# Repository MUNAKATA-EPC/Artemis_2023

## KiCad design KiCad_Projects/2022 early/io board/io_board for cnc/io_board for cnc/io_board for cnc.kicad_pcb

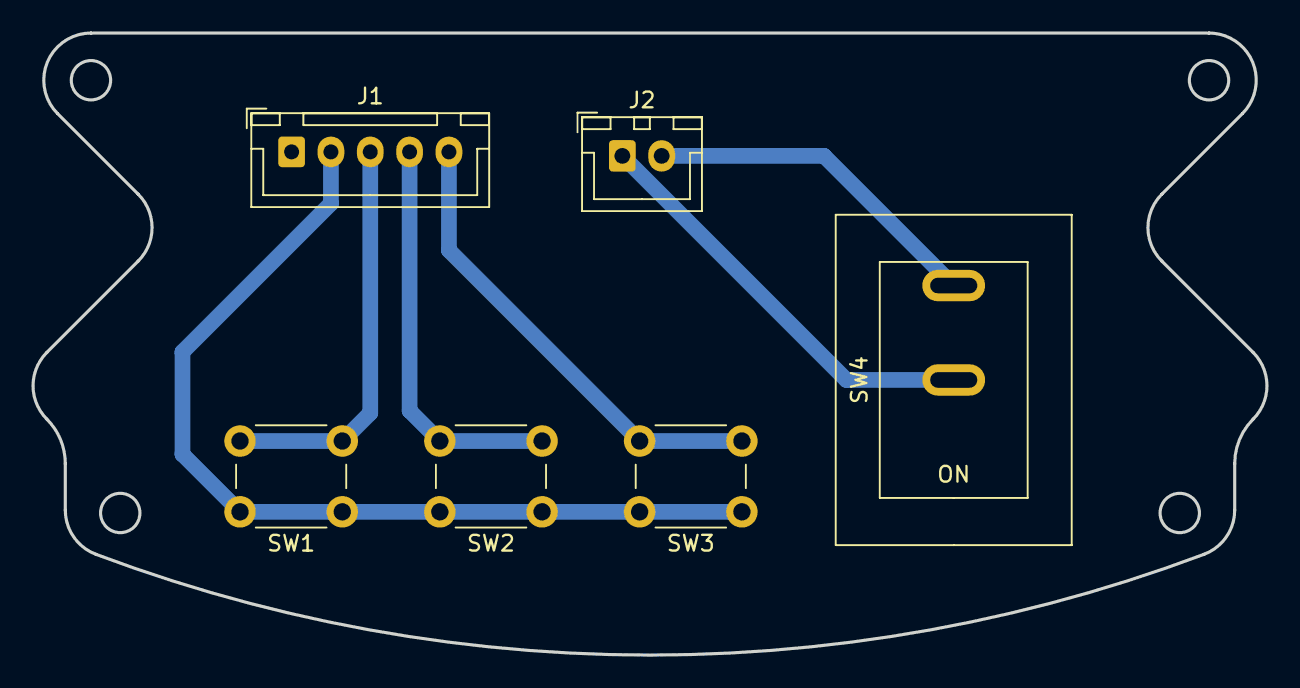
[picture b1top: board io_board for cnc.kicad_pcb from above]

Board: 2 copper layers, 78.4 x 39.5 mm, 6 parts (0 on the bottom side), 6 nets.

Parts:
J1: Conn_01x05_Female; JST_XH_B5B-XH-A_1x05_P2.50mm_Vertical
J2: Conn_01x02_Female; JST_XH_B2B-XH-A_1x02_P2.50mm_Vertical
SW1, SW2, SW3: SW_DIP_x01; SW_PUSH_6mm_H5mm
SW4: SW_DIP_x01; DS-850k

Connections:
+5V: J1.2, SW1.1, SW2.1, SW3.1
+7.5V: J2.2, SW4.2
GND: J2.1, SW4.1
SW1: J1.3, SW1.2
SW2: J1.4, SW2.2
SW3: J1.5, SW3.2

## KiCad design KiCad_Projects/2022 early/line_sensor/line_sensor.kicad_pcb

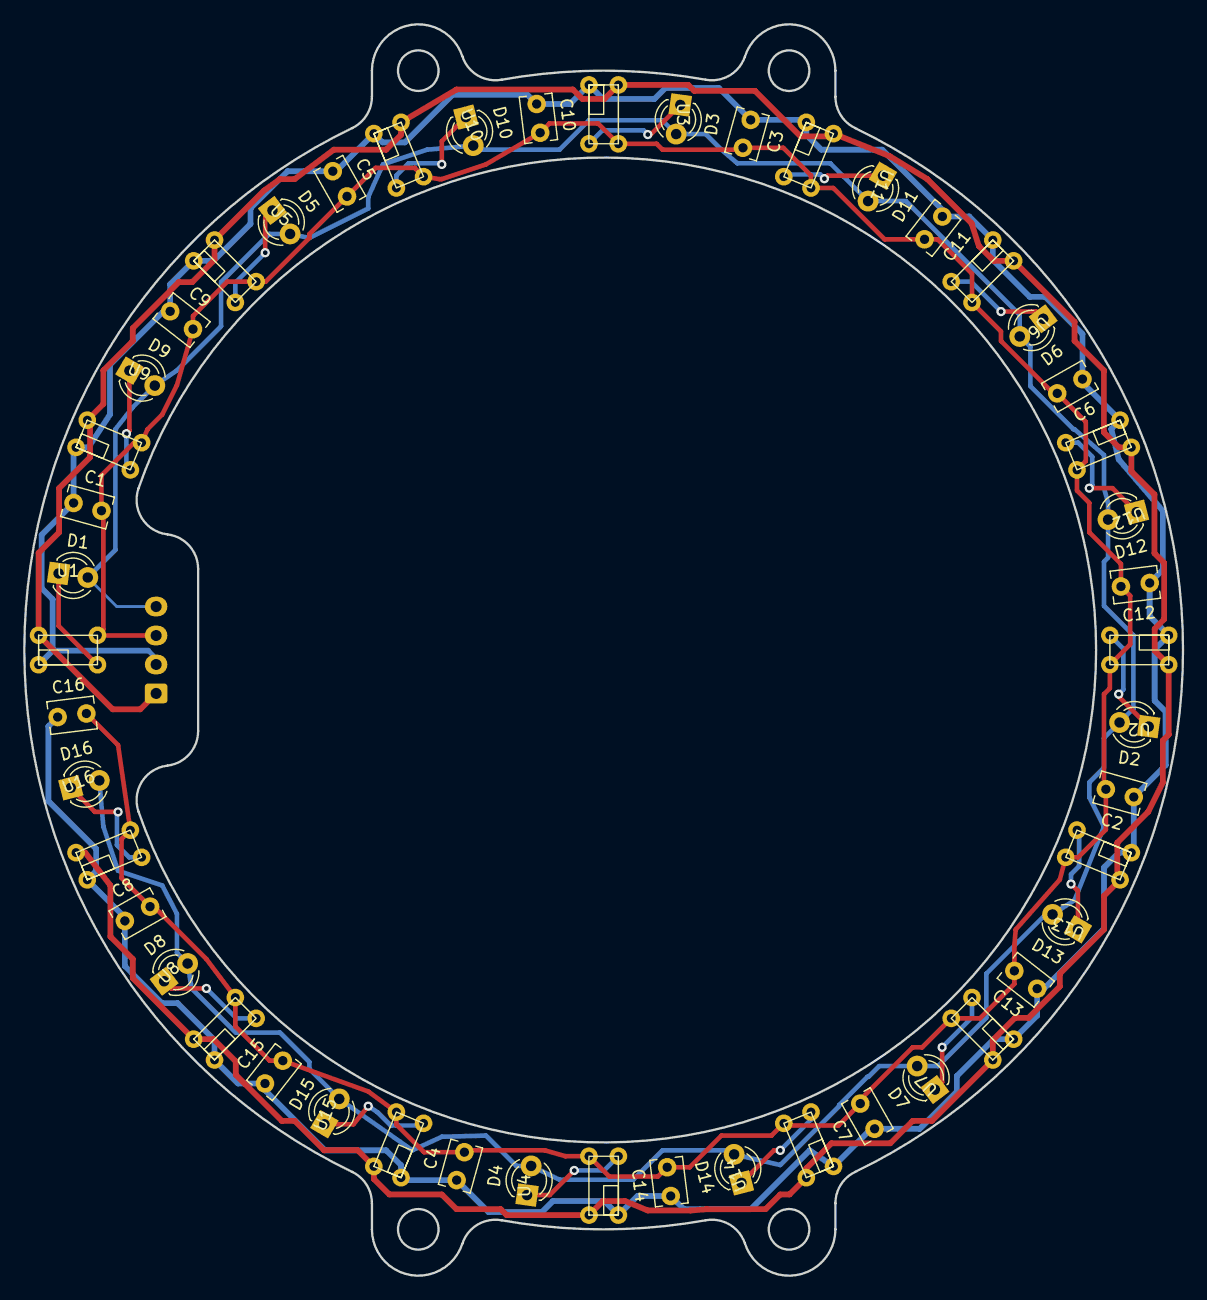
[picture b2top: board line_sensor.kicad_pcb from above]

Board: 2 copper layers, 100.0 x 108.0 mm, 49 parts (1 on the bottom side), 20 nets.

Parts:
C1, C2, C3, C4, C5, C6, C7, C8, C9, C10, C11, C12, C13, C14, C15, C16: C_Small; C_Disc_D3.8mm_W2.6mm_P2.50mm
D1, D2, D3, D4, D5, D6, D7, D8, D9, D10, D11, D12, D13, D14, D15, D16: LED; LED_D3.0mm_Clear
J1: Conn_01x04_Female; JST_XH_B4B-XH-A_1x04_P2.50mm_Vertical
U1, U2, U3, U4, U5, U6, U7, U8, U9, U10, U11, U12, U13, U14, U15, U16: S4282-51; Line_sennsor

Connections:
1: J1.1, U1.3 (Vout), U2.3 (Vout), U3.3 (Vout), U4.3 (Vout), U5.3 (Vout), U6.3 (Vout), U7.3 (Vout), U8.3 (Vout), U9.3 (Vout), U10.3 (Vout), U11.3 (Vout), U12.3 (Vout), U13.3 (Vout), U14.3 (Vout), U15.3 (Vout), U16.3 (Vout)
5: D1.2 (A), D2.2 (A), D3.2 (A), D4.2 (A), D5.2 (A), D6.2 (A), D7.2 (A), D8.2 (A), D9.2 (A), D10.2 (A), D11.2 (A), D12.2 (A), D13.2 (A), D14.2 (A), D15.2 (A), D16.2 (A), J1.4
+5V: C1.2, C2.2, C3.2, C4.2, C5.2, C6.2, C7.2, C8.2, C9.2, C10.2, C11.2, C12.2, C13.2, C14.2, C15.2, C16.2, J1.3, U1.2 (Vcc), U2.2 (Vcc), U3.2 (Vcc), U4.2 (Vcc), U5.2 (Vcc), U6.2 (Vcc), U7.2 (Vcc), U8.2 (Vcc), U9.2 (Vcc), U10.2 (Vcc), U11.2 (Vcc), U12.2 (Vcc), U13.2 (Vcc), U14.2 (Vcc), U15.2 (Vcc), U16.2 (Vcc)
GND: C1.1, C2.1, C3.1, C4.1, C5.1, C6.1, C7.1, C8.1, C9.1, C10.1, C11.1, C12.1, C13.1, C14.1, C15.1, C16.1, J1.2, U1.4 (GND), U2.4 (GND), U3.4 (GND), U4.4 (GND), U5.4 (GND), U6.4 (GND), U7.4 (GND), U8.4 (GND), U9.4 (GND), U10.4 (GND), U11.4 (GND), U12.4 (GND), U13.4 (GND), U14.4 (GND), U15.4 (GND), U16.4 (GND)
unnamed: D1.1 (K), U1.1 (K(-))
unnamed: D2.1 (K), U2.1 (K(-))
unnamed: D3.1 (K), U3.1 (K(-))
unnamed: D4.1 (K), U4.1 (K(-))
unnamed: D5.1 (K), U5.1 (K(-))
unnamed: D6.1 (K), U6.1 (K(-))
unnamed: D7.1 (K), U7.1 (K(-))
unnamed: D8.1 (K), U8.1 (K(-))
unnamed: D9.1 (K), U9.1 (K(-))
unnamed: D10.1 (K), U10.1 (K(-))
unnamed: D11.1 (K), U11.1 (K(-))
unnamed: D12.1 (K), U12.1 (K(-))
unnamed: D13.1 (K), U13.1 (K(-))
unnamed: D14.1 (K), U14.1 (K(-))
unnamed: D15.1 (K), U15.1 (K(-))
unnamed: D16.1 (K), U16.1 (K(-))

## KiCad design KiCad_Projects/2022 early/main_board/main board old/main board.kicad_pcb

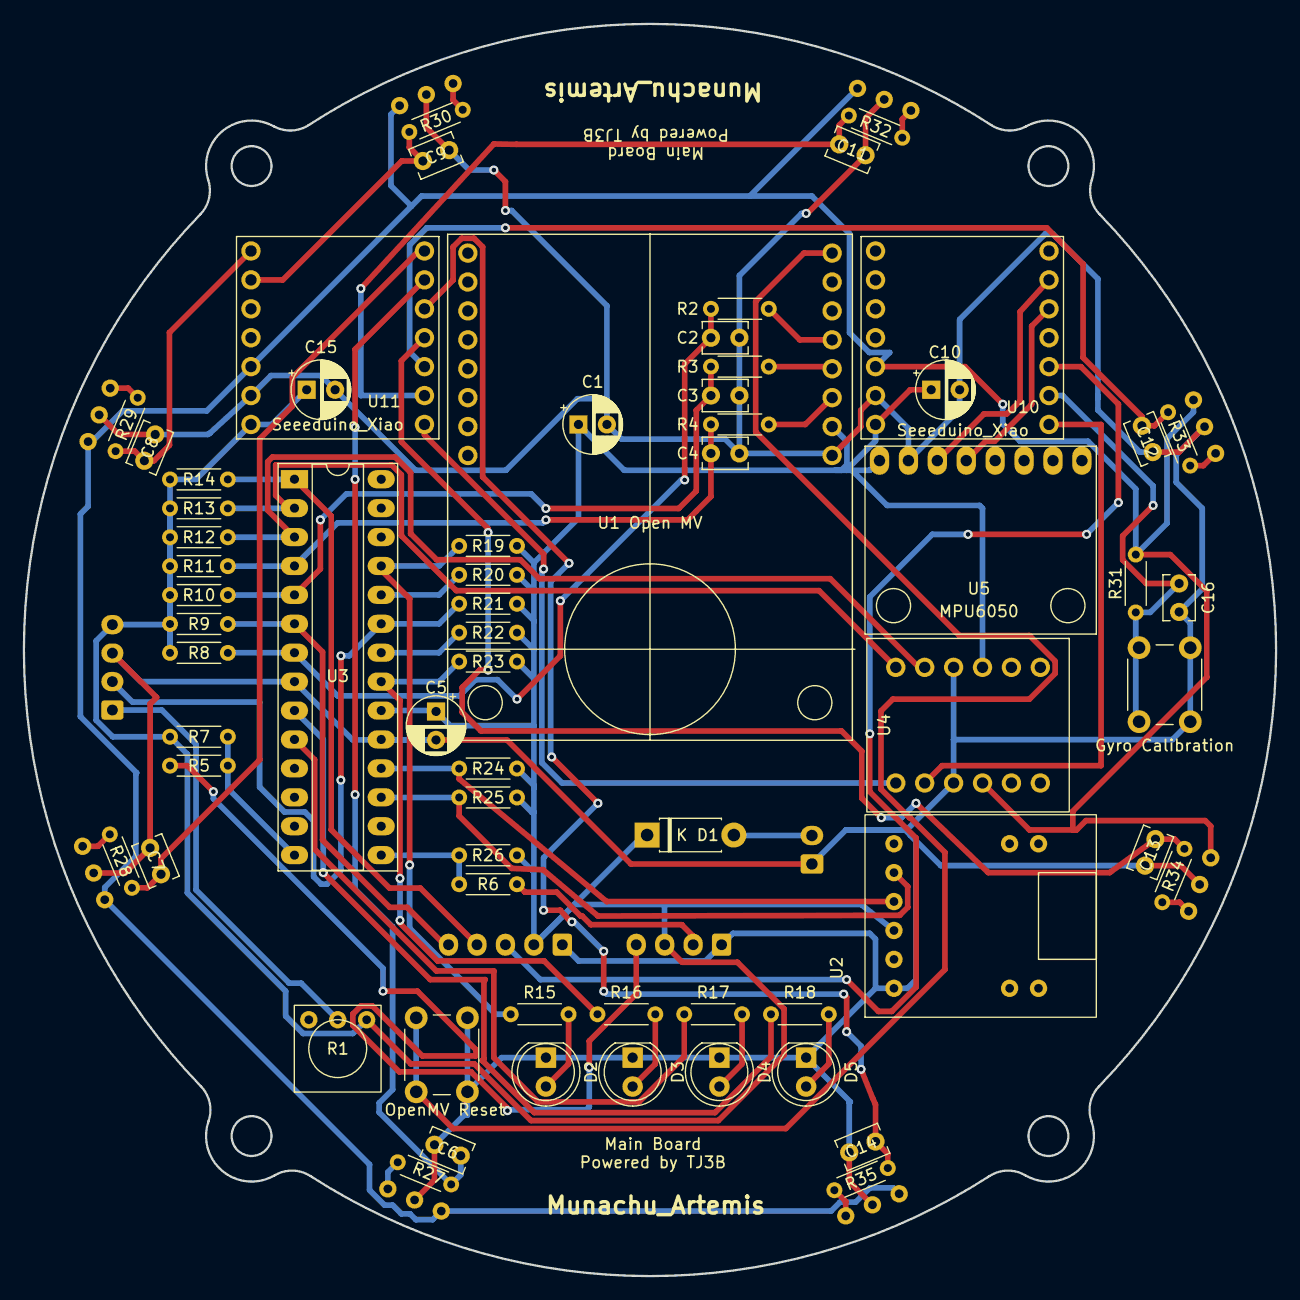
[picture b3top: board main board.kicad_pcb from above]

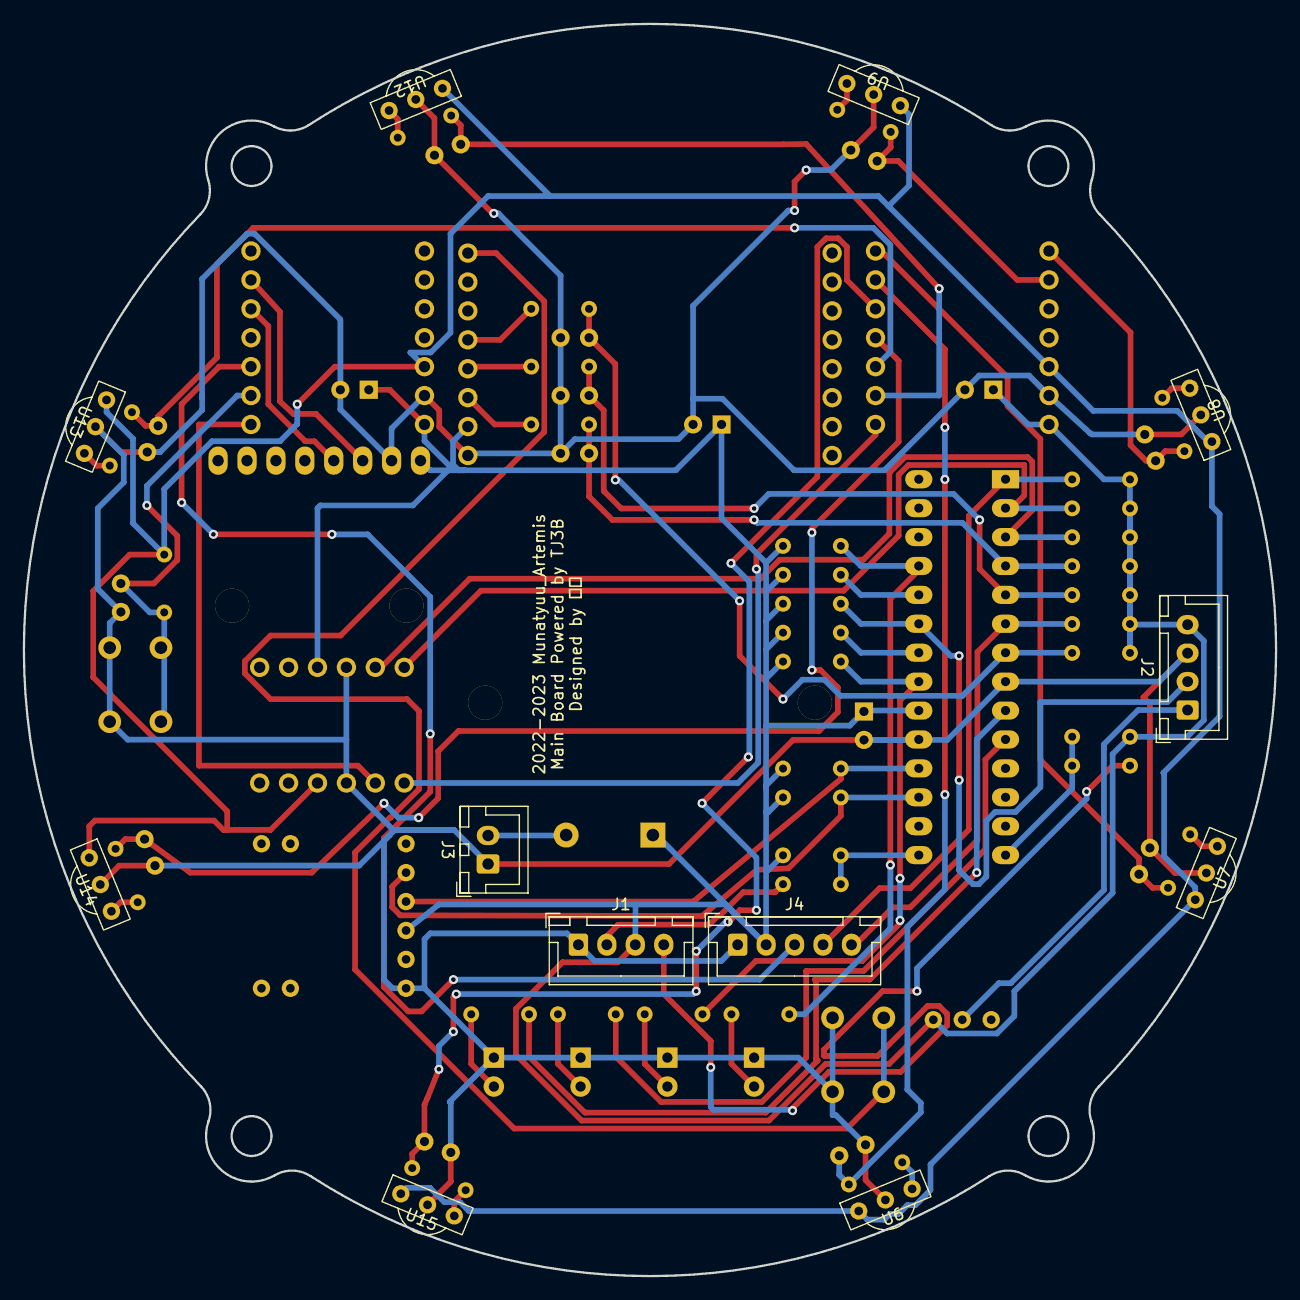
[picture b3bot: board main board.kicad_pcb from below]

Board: 2 copper layers, 110.0 x 110.0 mm, 77 parts (12 on the bottom side), 55 nets.

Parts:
C1, C5, C10, C15: C; CP_Radial_D5.0mm_P2.50mm
C2, C3, C4, C6, C7, C8, C9, C11, C12, C13, C14, C16: C_Small; C_Disc_D3.8mm_W2.6mm_P2.50mm
D1: D; D_DO-41_SOD81_P7.62mm_Horizontal
D2, D3, D4, D5: LED; LED_D5.0mm_Clear
Gyro Calibration: SW_Push; SW_PUSH_6mm_H5mm
J1, J2: Conn_01x04_Female; JST_XH_B4B-XH-A_1x04_P2.50mm_Vertical
J3: Conn_01x02_Female; JST_XH_B2B-XH-A_1x02_P2.50mm_Vertical
J4: Conn_01x05_Female; JST_XH_B5B-XH-A_1x05_P2.50mm_Vertical
OpenMV Reset: SW_Push; SW_PUSH_6mm_H5mm
R1: R_Variable; R_Varlable
R2, R3, R4, R31: R; R_Axial_DIN0204_L3.6mm_D1.6mm_P5.08mm_Horizontal
R5, R6, R7, R9, R14, R24, R25, R26: 10k; R_Axial_DIN0204_L3.6mm_D1.6mm_P5.08mm_Horizontal
R8, R10, R11, R12, R13, R19, R20, R21, R22, R23, R27, R28, R29, R30, R32, R33, R34, R35: 100k; R_Axial_DIN0204_L3.6mm_D1.6mm_P5.08mm_Horizontal
R15, R16, R17, R18: 330; R_Axial_DIN0204_L3.6mm_D1.6mm_P5.08mm_Horizontal
U1 Open MV: open_mv; OpenMV
U2: type-c_sirial; Type-C_Sirial_Board
U3: PIC18F26K20_ISS; DIP-28_W7.62mm_Socket_LongPads
U4: Akizuki_Logiv_Level_converter; Akizuki_Logic_Level_converter
U5: MPU6050
U6, U7, U8, U9, U12, U13, U14, U15: TSSP58038; TSSP58038_IR
U10, U11: Seeeduino_Xiao; seeeduinoXIAO

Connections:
+3V3: R31.1, U4.9 (LV), U6.2 (Vin), U7.2 (Vin), U8.2 (Vin), U9.2 (Vin), U10.12 (3V3), U11.12 (3V3), U12.2 (Vin), U13.2 (Vin), U14.2 (Vin), U15.2 (Vin)
+5V: C1.1, C5.1, C10.1, C15.1, D1.1 (K), J1.3, J2.4, J4.2, R1.1, R7.1, R8.1, R9.1, R10.1, R11.1, R12.1, R13.1, R14.1, R19.1, R20.1, R21.1, R22.1, R23.1, R24.1, R25.1, R26.1, U1 Open MV.10 (vin), U2.3 (VCC), U3.20 (Vdd), U4.4 (HV), U5.1 (VCC), U10.14 (5V), U11.14 (5V)
AD1: R13.2, U3.2 (RA0/AN0), U4.1 (HV1)
AD2: R12.2, U3.3 (RA1/AN1), U4.2 (HV2)
AD3: C4.1, R4.2, R11.2, U3.4 (RA2/Vref-AN2)
AD4: C3.1, R3.2, R10.2, U3.5 (RA3/Vref+AN3)
AD5: C2.1, R2.2, R8.2, U3.7 (RA5/AN4)
AD6: J2.2, R21.2, U3.23 (AN8/INT2/RB2)
AD7: R20.2, U3.24 (AN9/RB3)
AD8: R22.2, U3.22 (AN10/INT1/RB1)
AD9: R15.1, R19.2, U3.25 (AN11/RB4)
AD10: R16.1, R23.2, U3.21 (AN12/INT0/RB0)
GND: C1.2, C2.2, C3.2, C4.2, C5.2, C6.1, C7.1, C8.1, C9.1, C10.2, C11.2, C12.2, C13.2, C14.2, C15.2, C16.2, D2.1 (K), D3.1 (K), D4.1 (K), D5.1 (K), Gyro Calibration.2, J1.1, J2.3, J3.1, J4.1, OpenMV Reset.2, U1 Open MV.9 (gnd), U2.1 (GND), U3.8 (Vss), U3.19 (Vss), U4.3 (GND), U4.10 (GND), U5.2 (GND), U6.1 (GND), U7.1 (GND), U8.1 (GND), U9.1 (GND), U10.13 (GND), U11.13 (GND), U12.1 (GND), U13.1 (GND), U14.1 (GND), U15.1 (GND)
IR1: C11.1, R32.1, U11.2
IR2: C12.1, R33.1, U11.3
IR3: C13.1, R34.1, U11.4
IR4: C14.1, R35.1, U11.5 (SDA)
IR5: C6.2, R27.2, U11.6 (SCL)
IR6: C7.2, R28.2, U11.7 (TX)
IR7: C8.2, R29.2, U11.8 (RX)
IR8: C9.2, R30.2, U11.9 (SCK)
LV1: U4.12 (LV1), U11.1 (DAC)
LV2: U4.11 (LV2), U10.1 (DAC)
MCLR: J4.4, R14.2, U3.1 (~MCLR/RE3)
MON LED: R17.1, U3.10 (RA6/OSC2/CLKOUT)
unnamed: D1.2 (A), J3.2
unnamed: D2.2 (A), R15.2
unnamed: D3.2 (A), R16.2
unnamed: D4.2 (A), R17.2
unnamed: D5.2 (A), R18.2
unnamed: J1.2, R6.1
unnamed: J1.4, R5.1
unnamed: J2.1, R1.2
unnamed: R2.1, U1 Open MV.13 (seru03)
unnamed: R3.1, U1 Open MV.12 (seru02)
unnamed: R4.1, U1 Open MV.11 (seru01)
unnamed: OpenMV Reset.1, U1 Open MV.16 (rst)
unnamed: R27.1, U6.0 (OUT)
unnamed: R28.1, U7.0 (OUT)
unnamed: R29.1, U8.0 (OUT)
unnamed: R30.1, U9.0 (OUT)
unnamed: U5.4 (SDA), U10.5 (SDA)
unnamed: U5.3 (SCL), U10.6 (SCL)
unnamed: R32.2, U12.0 (OUT)
unnamed: R33.2, U13.0 (OUT)
unnamed: R34.2, U14.0 (OUT)
unnamed: R35.2, U15.0 (OUT)
PWR LED: R18.1, U3.9 (RA7/OSC1/CLKIN)
RA4: J4.5, R9.2, U3.6 (RA4)
RES: C16.1, Gyro Calibration.1, R31.2, U10.2
RX: R24.2, U2.4 (TXD), U3.18 (RX/RC7)
SCL: R5.2, R7.2, U3.14 (SCL/SCK/RC3)
SDA: R6.2, R26.2, U3.15 (SDA/SDI/RC4)
SW2: J4.3, U10.3
TX: R25.2, U2.5 (RXD), U3.17 (TX/RC6)

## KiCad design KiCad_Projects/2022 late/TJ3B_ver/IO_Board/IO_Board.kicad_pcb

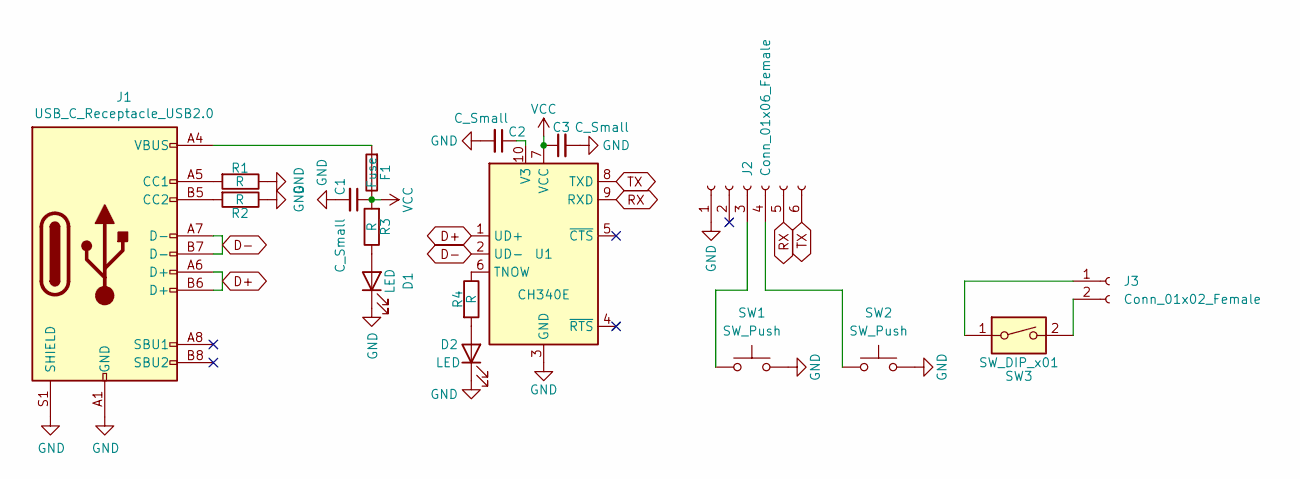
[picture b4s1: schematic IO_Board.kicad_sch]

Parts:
C1: C_Small; C_01005_0402Metric; LCSC C194427
C2, C3: C_Small; C_01005_0402Metric; LCSC C126469
D1, D2: LED; LED_0402_1005Metric; LCSC C84263
F1: Fuse; Fuse_0603_1608Metric; LCSC C116602
J1: USB_C_Receptacle_USB2.0; USB_C_Receptacle_XKB_U262-16XN-4BVC11; LCSC C2760486
J2: Conn_01x06_Female; JST_XH_B6B-XH-A_1x06_P2.50mm_Vertical
J3: Conn_01x02_Female; JST_XH_B2B-XH-A_1x02_P2.50mm_Vertical
R1, R2: R; R_0402_1005Metric; LCSC C159886
R3: R; R_0603_1608Metric; LCSC C105428
R4: R; R_0402_1005Metric; LCSC C159884
SW1, SW2: SW_Push; SW_PUSH_6mm_H5mm
SW3: SW_DIP_x01; DS-850k
U1: CH340E; MSOP-10_3x3mm_P0.5mm; LCSC C99652

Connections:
D+: J1.A6 (D+), J1.B6 (D+), U1.1 (UD+)
D-: J1.A7 (D-), J1.B7 (D-), U1.2 (UD-)
GND: C1.2, C2.2, C3.2, D1.1 (K), D2.1 (K), J1.A1 (GND), J1.A12 (GND), J1.B1 (GND), J1.B12 (GND), J1.S1 (SHIELD), J2.1, R1.1, R2.1, SW1.2, SW2.2, U1.3 (GND)
unnamed: C2.1, U1.10 (V3)
unnamed: D1.2 (A), R3.1
unnamed: D2.2 (A), R4.2
unnamed: F1.2, J1.A4 (VBUS), J1.A9 (VBUS), J1.B4 (VBUS), J1.B9 (VBUS)
unnamed: J1.A5 (CC1), R1.2
unnamed: J1.B5 (CC2), R2.2
unnamed: J2.3, SW1.1
unnamed: J2.4, SW2.1
unnamed: J3.1, SW3.1
unnamed: J3.2, SW3.2
unnamed: R4.1, U1.6 (TNOW)
RX: J2.5, U1.9 (RXD)
TX: J2.6, U1.8 (TXD)
VCC: C1.1, C3.1, F1.1, R3.2, U1.7 (VCC)

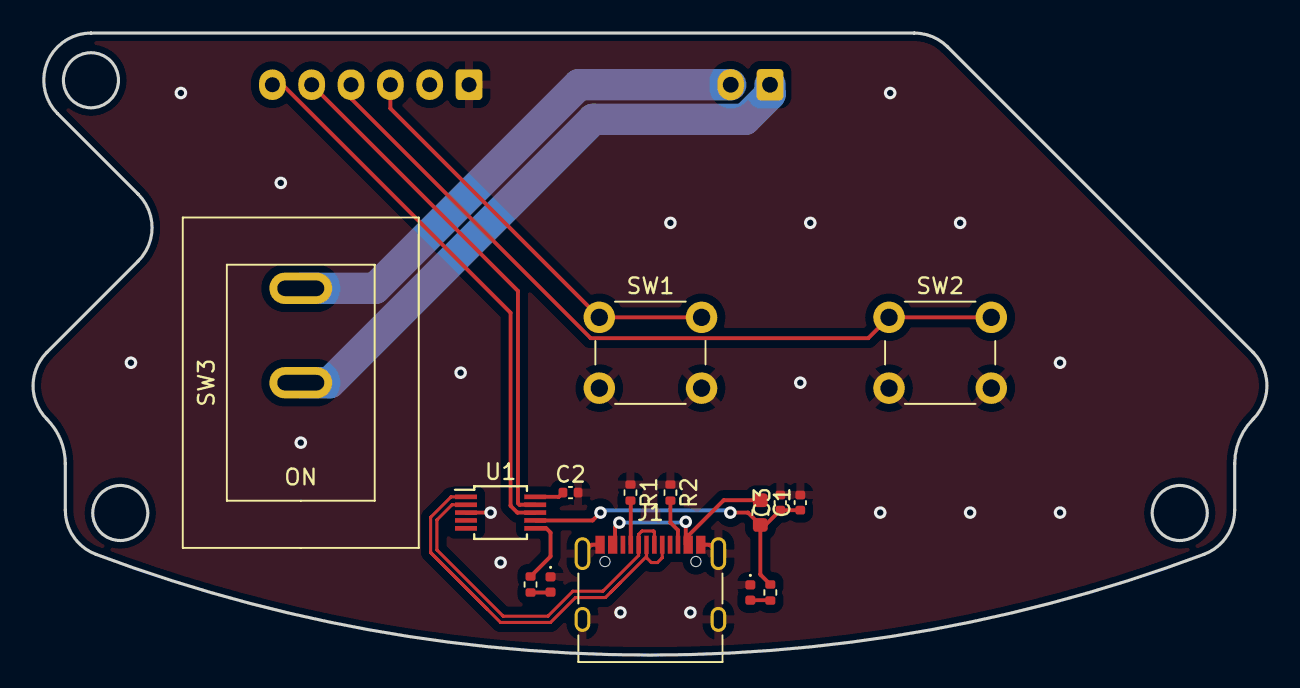
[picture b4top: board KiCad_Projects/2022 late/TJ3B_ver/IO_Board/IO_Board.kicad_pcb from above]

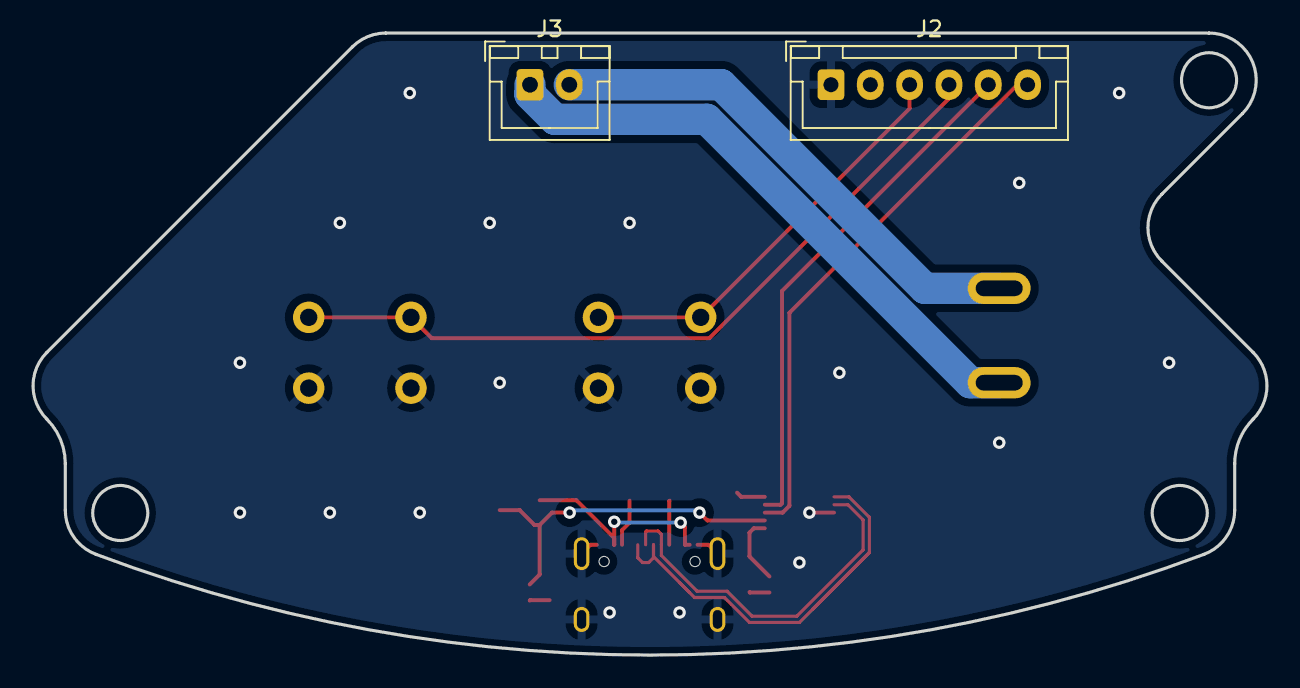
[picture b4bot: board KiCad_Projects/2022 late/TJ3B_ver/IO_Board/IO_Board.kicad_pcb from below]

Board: 2 copper layers, 78.4 x 39.5 mm, 17 parts (2 on the bottom side), 17 nets.

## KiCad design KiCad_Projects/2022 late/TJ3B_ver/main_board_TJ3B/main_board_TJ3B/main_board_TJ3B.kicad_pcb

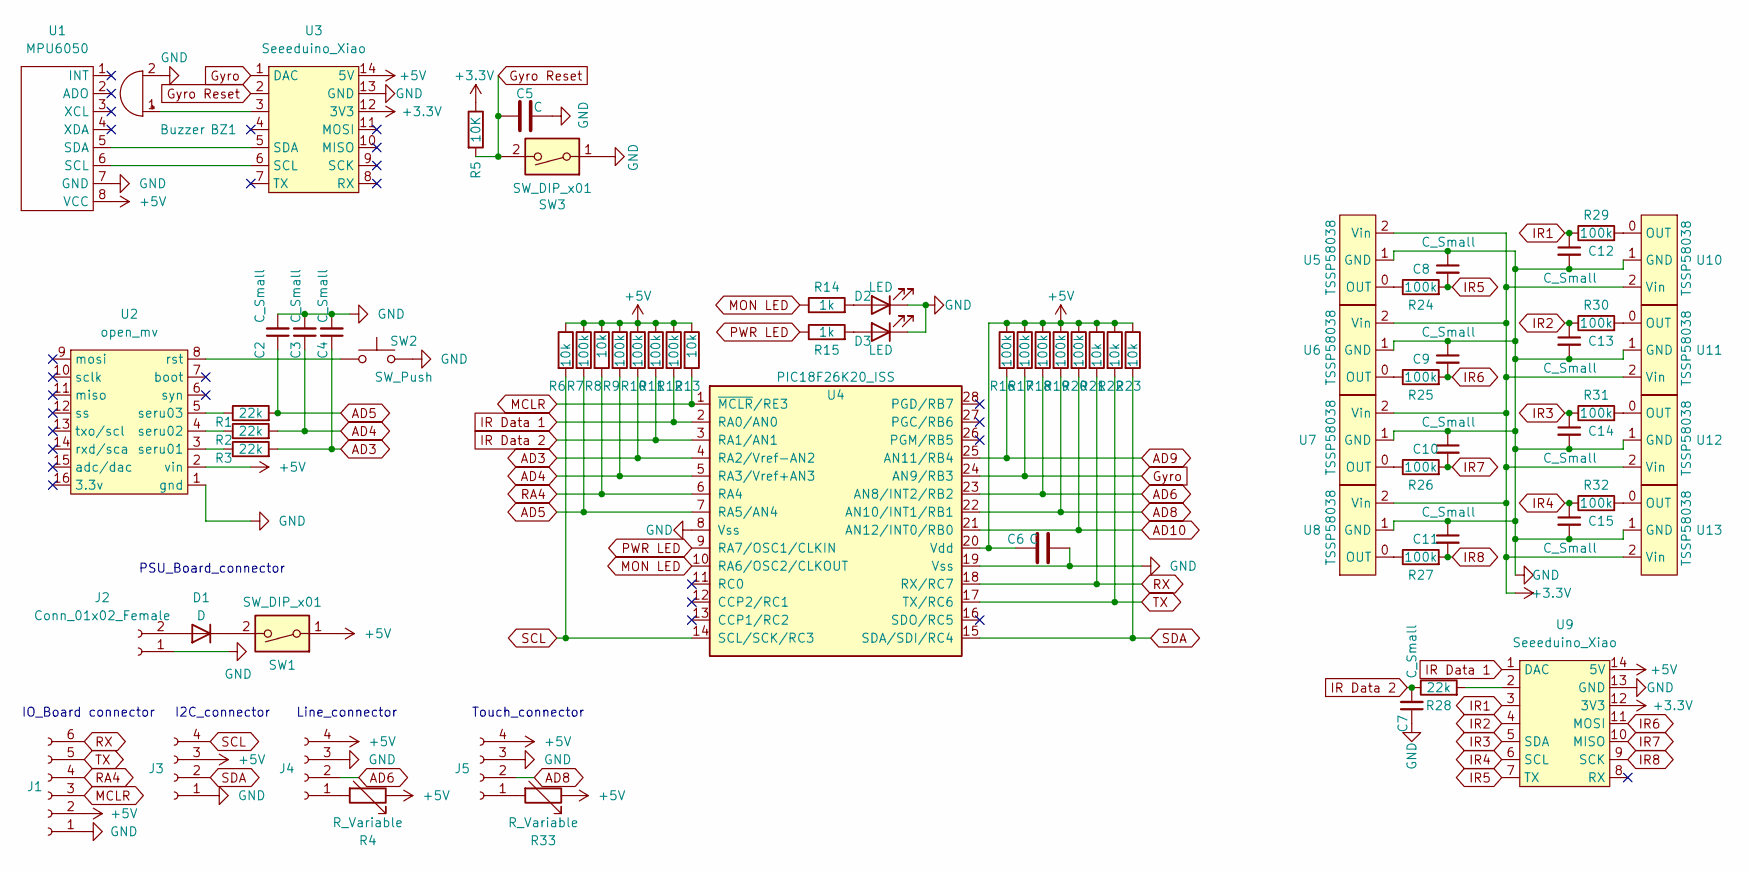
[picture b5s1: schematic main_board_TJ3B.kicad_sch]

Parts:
BZ1: Buzzer; Buzzer_12x9.5RM7.6
C2, C3, C4, C7: C_Small; C_0402_1005Metric; LCSC C528972
C5: C; C_0402_1005Metric; LCSC C507422
C6: C; CP_Radial_D5.0mm_P2.50mm
C8, C9, C10, C11, C12, C13, C14, C15: C_Small; C_0402_1005Metric; LCSC C507422
D1: D; D_DO-41_SOD81_P7.62mm_Horizontal
D2, D3: LED; LED_0402_1005Metric; LCSC C130725
J1: Conn_01x06_Female; JST_XH_B6B-XH-A_1x06_P2.50mm_Vertical
J2: Conn_01x02_Female; JST_XH_B2B-XH-A_1x02_P2.50mm_Vertical
J3, J4, J5: Conn_01x04_Female; JST_XH_B4B-XH-A_1x04_P2.50mm_Vertical
R1, R2, R3, R28: 22k; R_0402_1005Metric; LCSC C25768
R4, R33: R_Variable; 可変抵抗(小)
R5: 10K; R_0402_1005Metric; LCSC C269674
R6, R8, R13, R21, R22, R23: 10k; R_0402_1005Metric; LCSC C269674
R7, R9, R10, R11, R12, R16, R17, R18, R19, R20, R24, R25, R26, R27, R29, R30, R31, R32: 100k; R_0402_1005Metric; LCSC C269673
R14, R15: 1k; R_0402_1005Metric; LCSC C11702
SW1: SW_DIP_x01; 2MS1T2B4M2QES
SW2: SW_Push; SW_PUSH_6mm_H5mm
SW3: SW_DIP_x01; SW_PUSH_6mm_H5mm
U1: MPU6050
U2: open_mv; OpenMV
U3, U9: Seeeduino_Xiao; seeeduinoXIAO
U4: PIC18F26K20_ISS; DIP-28_W7.62mm_Socket
U5, U6, U7, U8, U10, U11, U12, U13: TSSP58038; TSSP58038_IR

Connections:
+3V3: R5.1, U3.12 (3V3), U5.2 (Vin), U6.2 (Vin), U7.2 (Vin), U8.2 (Vin), U9.12 (3V3), U10.2 (Vin), U11.2 (Vin), U12.2 (Vin), U13.2 (Vin)
+5V: C6.1, J1.2, J3.3, J4.4, J5.4, R4.1, R6.1, R7.1, R8.1, R9.1, R10.1, R11.1, R12.1, R13.1, R16.1, R17.1, R18.1, R19.1, R20.1, R21.1, R22.1, R23.1, R33.1, SW1.1, U1.8 (VCC), U2.2 (vin), U3.14 (5V), U4.20 (Vdd), U9.14 (5V)
AD3: C4.1, R3.2, R10.2, U4.4 (RA2/Vref-AN2)
AD4: C3.1, R2.2, R9.2, U4.5 (RA3/Vref+AN3)
AD5: C2.1, R1.2, R7.2, U4.7 (RA5/AN4)
AD6: J4.2, R18.2, U4.23 (AN8/INT2/RB2)
AD8: J5.2, R19.2, U4.22 (AN10/INT1/RB1)
AD9: R16.2, U4.25 (AN11/RB4)
AD10: R20.2, U4.21 (AN12/INT0/RB0)
GND: BZ1.2 (+), C2.2, C3.2, C4.2, C5.2, C6.2, C7.1, C8.1, C9.1, C10.1, C11.1, C12.2, C13.2, C14.2, C15.2, D2.1 (K), D3.1 (K), J1.1, J2.1, J3.1, J4.3, J5.3, SW2.2, SW3.1, U1.7 (GND), U2.1 (gnd), U3.13 (GND), U4.8 (Vss), U4.19 (Vss), U5.1 (GND), U6.1 (GND), U7.1 (GND), U8.1 (GND), U9.13 (GND), U10.1 (GND), U11.1 (GND), U12.1 (GND), U13.1 (GND)
Gyro: R17.2, U3.1 (DAC), U4.24 (AN9/RB3)
Gyro Reset: C5.1, R5.2, SW3.2, U3.2
IR1: C12.1, R29.1, U9.3
IR2: C13.1, R30.1, U9.4
IR3: C14.1, R31.1, U9.5 (SDA)
IR4: C15.1, R32.1, U9.6 (SCL)
IR5: C8.2, R24.2, U9.7 (TX)
IR6: C9.2, R25.2, U9.11 (MOSI)
IR7: C10.2, R26.2, U9.10 (MISO)
IR8: C11.2, R27.2, U9.9 (SCK)
IR Data 1: R12.2, U4.2 (RA0/AN0), U9.1 (DAC)
IR Data 2: C7.2, R11.2, R28.1, U4.3 (RA1/AN1)
MCLR: J1.3, R13.2, U4.1 (~MCLR/RE3)
MON LED: R14.1, U4.10 (RA6/OSC2/CLKOUT)
unnamed: BZ1.1 (-), U3.3
unnamed: D1.1 (K), SW1.2
unnamed: D1.2 (A), J2.2
unnamed: D2.2 (A), R14.2
unnamed: D3.2 (A), R15.2
unnamed: J4.1, R4.2
unnamed: J5.1, R33.2
unnamed: R1.1, U2.5 (seru03)
unnamed: R2.1, U2.4 (seru02)
unnamed: R3.1, U2.3 (seru01)
unnamed: R24.1, U5.0 (OUT)
unnamed: R25.1, U6.0 (OUT)
unnamed: R26.1, U7.0 (OUT)
unnamed: R27.1, U8.0 (OUT)
unnamed: R28.2, U9.2
unnamed: R29.2, U10.0 (OUT)
unnamed: R30.2, U11.0 (OUT)
unnamed: R31.2, U12.0 (OUT)
unnamed: R32.2, U13.0 (OUT)
unnamed: SW2.1, U2.8 (rst)
unnamed: U1.5 (SDA), U3.5 (SDA)
unnamed: U1.6 (SCL), U3.6 (SCL)
PWR LED: R15.1, U4.9 (RA7/OSC1/CLKIN)
RA4: J1.4, R8.2, U4.6 (RA4)
RX: J1.6, R21.2, U4.18 (RX/RC7)
SCL: J3.4, R6.2, U4.14 (SCL/SCK/RC3)
SDA: J3.2, R23.2, U4.15 (SDA/SDI/RC4)
TX: J1.5, R22.2, U4.17 (TX/RC6)

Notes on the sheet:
Touch_connector
PSU_Board_connector
Line_connector
I2C_connector
IO_Board connector

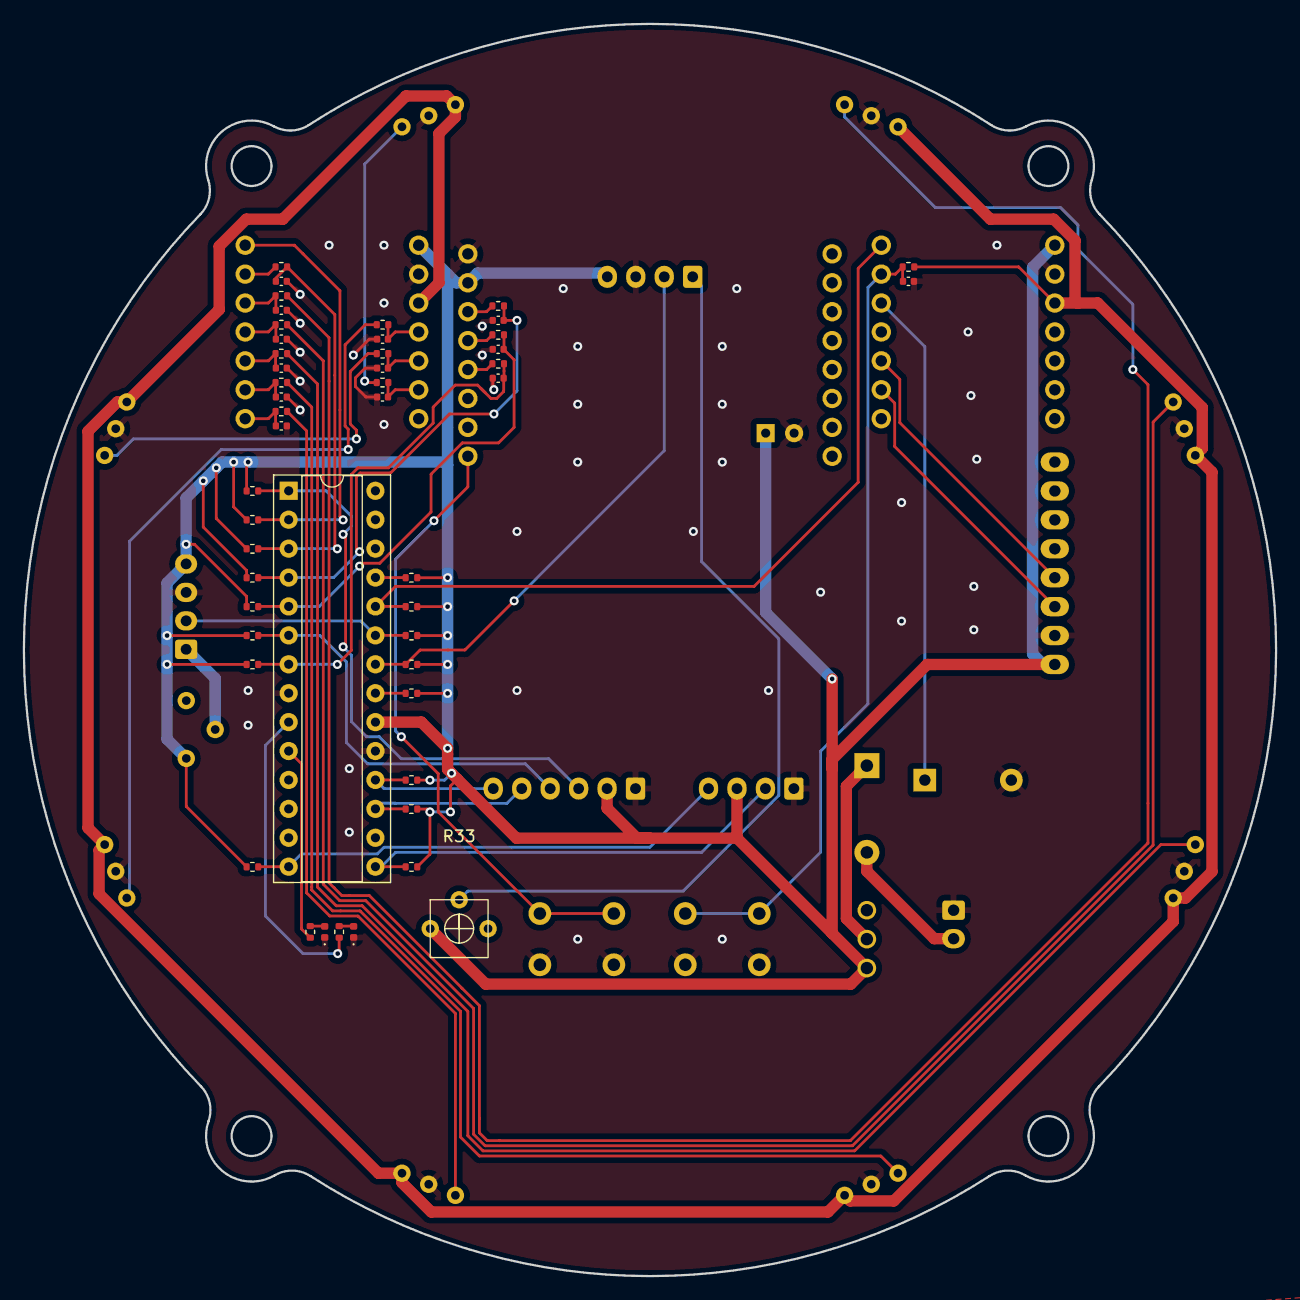
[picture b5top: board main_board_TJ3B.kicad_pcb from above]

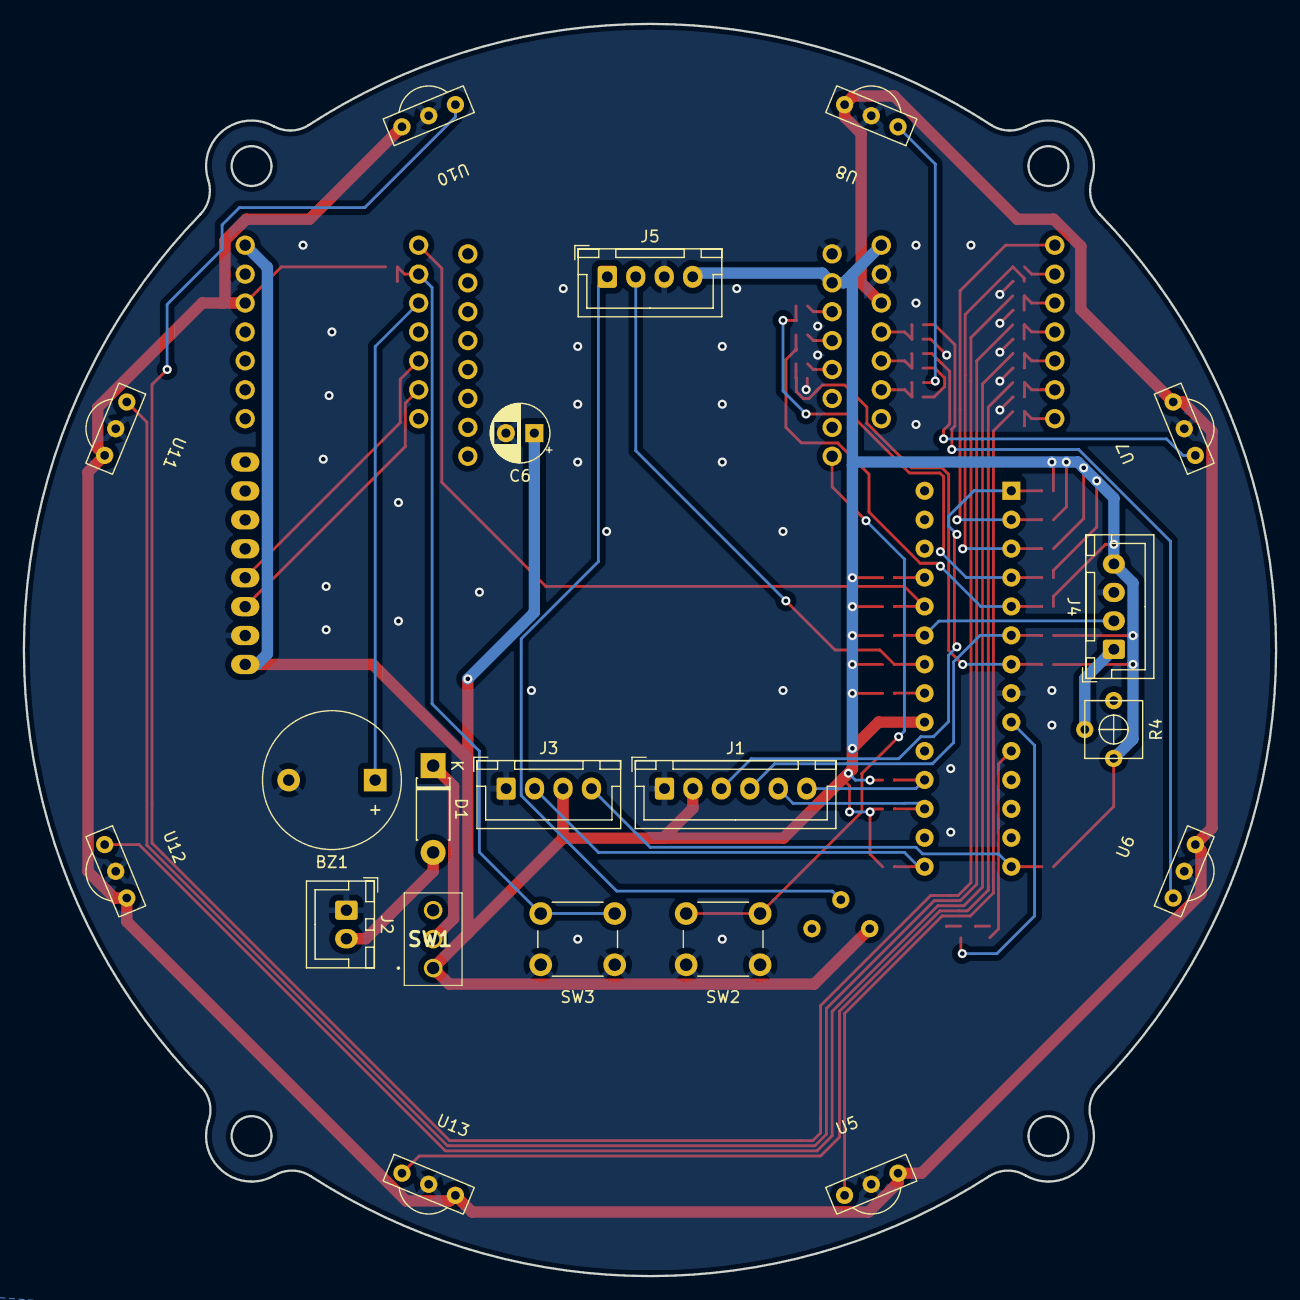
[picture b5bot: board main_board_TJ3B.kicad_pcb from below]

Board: 2 copper layers, 110.0 x 110.0 mm, 72 parts (21 on the bottom side), 52 nets.
